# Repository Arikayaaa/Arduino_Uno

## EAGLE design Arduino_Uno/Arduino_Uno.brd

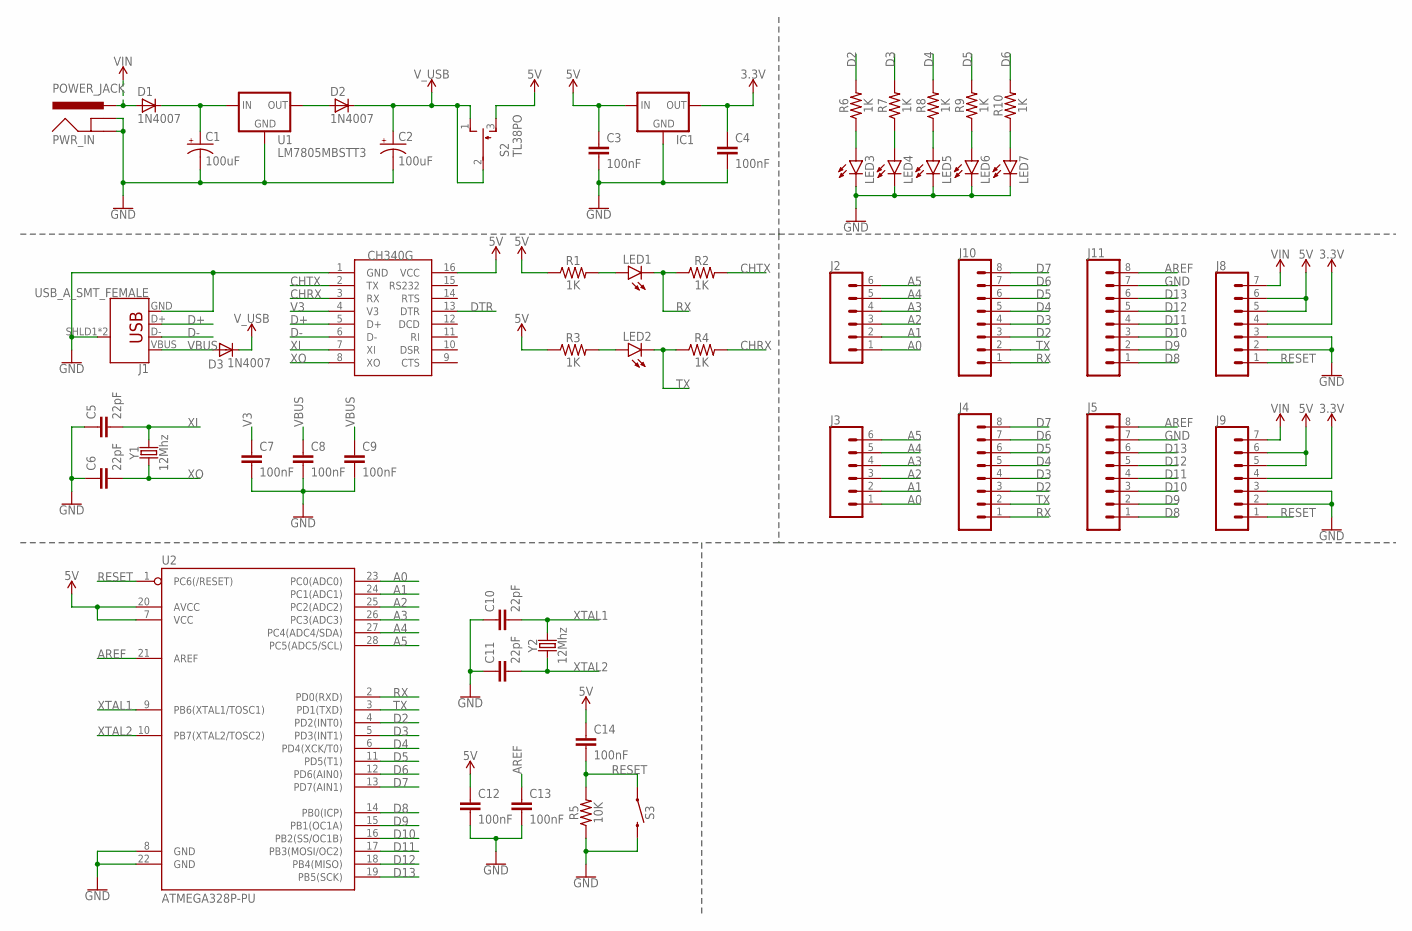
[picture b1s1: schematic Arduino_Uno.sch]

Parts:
C1, C2: 100uF; PANASONIC_D
C3, C4, C7, C8, C9, C12, C13, C14: 100nF; 0805
C5, C6, C10, C11: 22pF; 0805
D1, D2, D3: 1N4007; SMA
IC1: LM1117; SOT223
J1: USB_A_SMT_FEMALE; USB-A-S-SILK-FEMALE
J2, J3: CONN_06NO_SILK_FEMALE_PTH; 1X06_NO_SILK
J4, J5, J10, J11: CONN_08"; 1X08
J8, J9: CONN_07; 1X07
LED1, LED2, LED3, LED4, LED5, LED6, LED7: LEDSML0805; SML0805
PWR_IN: POWER_JACK; POWER_JACK_PTH
R1, R2, R3, R4, R6, R7, R8, R9, R10: 1K; 0805
R5: 10K; 0805
S2: TL38PO; TL3XPO
S3: MOMENTARY-SWITCH-SPST-PTH-6.0MM; TACTILE_SWITCH_PTH_6.0MM
U1: LM7805MBSTT3; D2PAK
U2: ATMEGA328P-PU; DIP28
U$1: CH340G; SOIC16
Y1, Y2: 12Mhz; HC49UP

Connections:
3.3V: C4.1, IC1.2 (OUT), J8.4, J9.4
5V: C3.1, C12.1, C14.1, IC1.3 (IN), J8.5, J8.6, J9.5, J9.6, R1.1, R3.1, S2.3 (S), U2.7 (VCC), U2.20 (AVCC), U$1.16 (VCC)
A0: J2.1, J3.1, U2.23 (PC0(ADC0))
A1: J2.2, J3.2, U2.24 (PC1(ADC1))
A2: J2.3, J3.3, U2.25 (PC2(ADC2))
A3: J2.4, J3.4, U2.26 (PC3(ADC3))
A4: J2.5, J3.5, U2.27 (PC4(ADC4/SDA))
A5: J2.6, J3.6, U2.28 (PC5(ADC5/SCL))
AREF: C13.1, J5.8, J11.8, U2.21 (AREF)
CHRX: R4.2, U$1.3 (RX)
CHTX: R2.2, U$1.2 (TX)
D2: J4.3, J10.3, R6.2, U2.4 (PD2(INT0))
D3: J4.4, J10.4, R7.2, U2.5 (PD3(INT1))
D4: J4.5, J10.5, R8.2, U2.6 (PD4(XCK/T0))
D5: J4.6, J10.6, R9.2, U2.11 (PD5(T1))
D6: J4.7, J10.7, R10.2, U2.12 (PD6(AIN0))
D7: J4.8, J10.8, U2.13 (PD7(AIN1))
D8: J5.1, J11.1, U2.14 (PB0(ICP))
D9: J5.2, J11.2, U2.15 (PB1(OC1A))
D10: J5.3, J11.3, U2.16 (PB2(SS/OC1B))
D11: J5.4, J11.4, U2.17 (PB3(MOSI/OC2))
D12: J5.5, J11.5, U2.18 (PB4(MISO))
D13: J5.6, J11.6, U2.19 (PB5(SCK))
D+: J1.D+, U$1.5 (D+)
D-: J1.D-, U$1.6 (D-)
DTR: U$1.13 (DTR)
GND: C1.-, C2.-, C3.2, C4.2, C5.1, C6.1, C7.2, C8.2, C9.2, C10.1, C11.1, C12.2, C13.2, IC1.1 (GND), J1.GND, J1.SHLD1 (SHIELD), J1.SHLD2 (SHIELD), J5.7, J8.2, J8.3, J9.2, J9.3, J11.7, LED3.C, LED4.C, LED5.C, LED6.C, LED7.C, PWR_IN.GND, PWR_IN.GNDBREAK, R5.1, S3.3 (2), U1.2 (GND), U2.8 (GND), U2.22 (GND), U$1.1 (GND)
unnamed: C1.+, D1.K (C), U1.1 (IN)
unnamed: D2.A, U1.3 (OUT)
unnamed: LED2.A, R3.2
unnamed: LED1.A, R1.2
unnamed: LED3.A, R6.1
unnamed: LED4.A, R7.1
unnamed: LED5.A, R8.1
unnamed: LED6.A, R9.1
unnamed: LED7.A, R10.1
RESET: C14.2, J8.1, J9.1, R5.2, S3.1, U2.1 (PC6(/RESET))
RX: J4.1, J10.1, LED1.C, R2.1, U2.2 (PD0(RXD))
TX: J4.2, J10.2, LED2.C, R4.1, U2.3 (PD1(TXD))
V3: C7.1, U$1.4 (V3)
VBUS: C8.1, C9.1, D3.A, J1.VBUS
VIN: D1.A, J8.7, J9.7, PWR_IN.PWR
V_USB: C2.+, D2.K (C), D3.K (C), S2.1 (O), S2.2
XI: C5.2, U$1.7 (XI), Y1.2
XO: C6.2, U$1.8 (XO), Y1.1
XTAL1: C10.2, U2.9 (PB6(XTAL1/TOSC1)), Y2.2
XTAL2: C11.2, U2.10 (PB7(XTAL2/TOSC2)), Y2.1

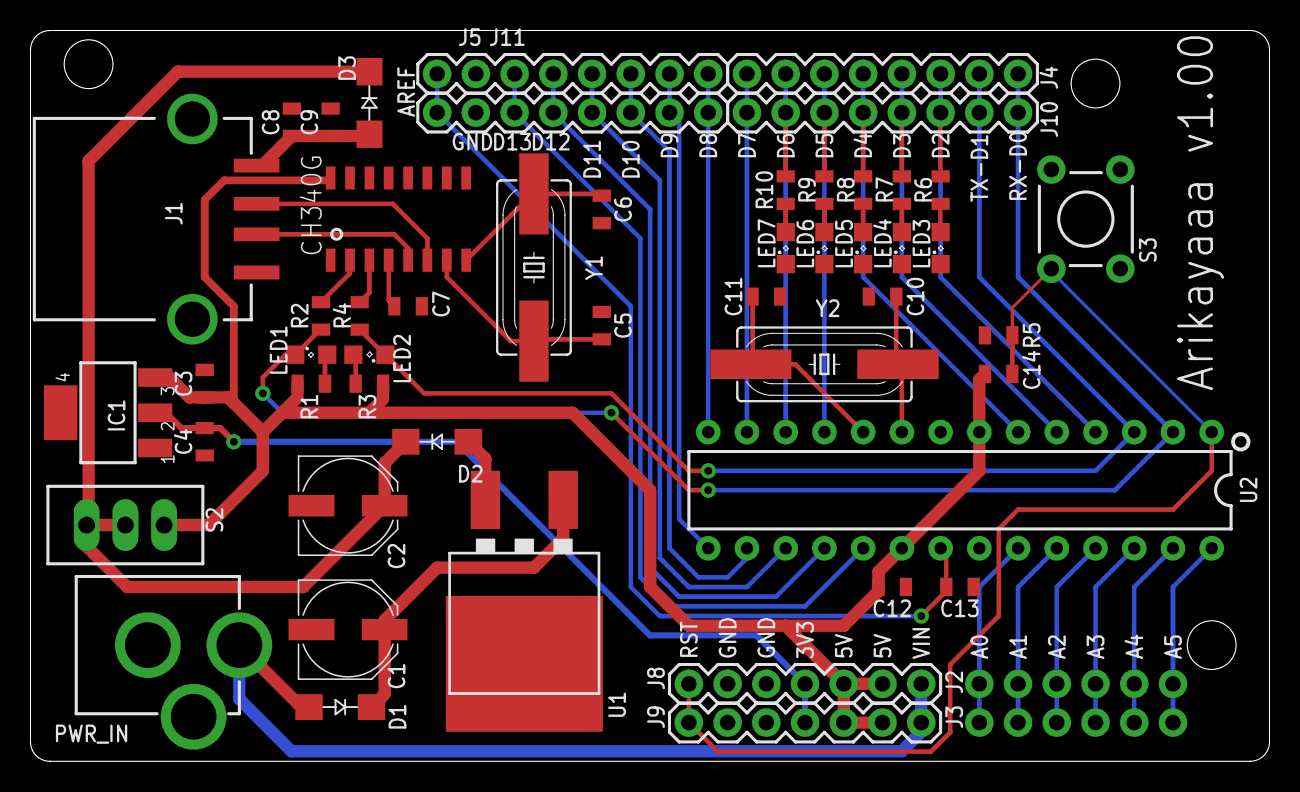
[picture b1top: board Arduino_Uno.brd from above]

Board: 2 copper layers, 81.3 x 47.9 mm, 52 parts (0 on the bottom side), 46 nets.

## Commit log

2020-05-26 v1.00
2020-05-26 v1.01
    Gerber files added
2022-05-19 v1.02
    Unnecessary recovery files were deleted.

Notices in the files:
parts and their libraries:
SparkFun-Capacitors: Licensing: Creative Commons ShareAlike 4.0 International - https://creativecommons.org/licenses/by-sa/4.0
